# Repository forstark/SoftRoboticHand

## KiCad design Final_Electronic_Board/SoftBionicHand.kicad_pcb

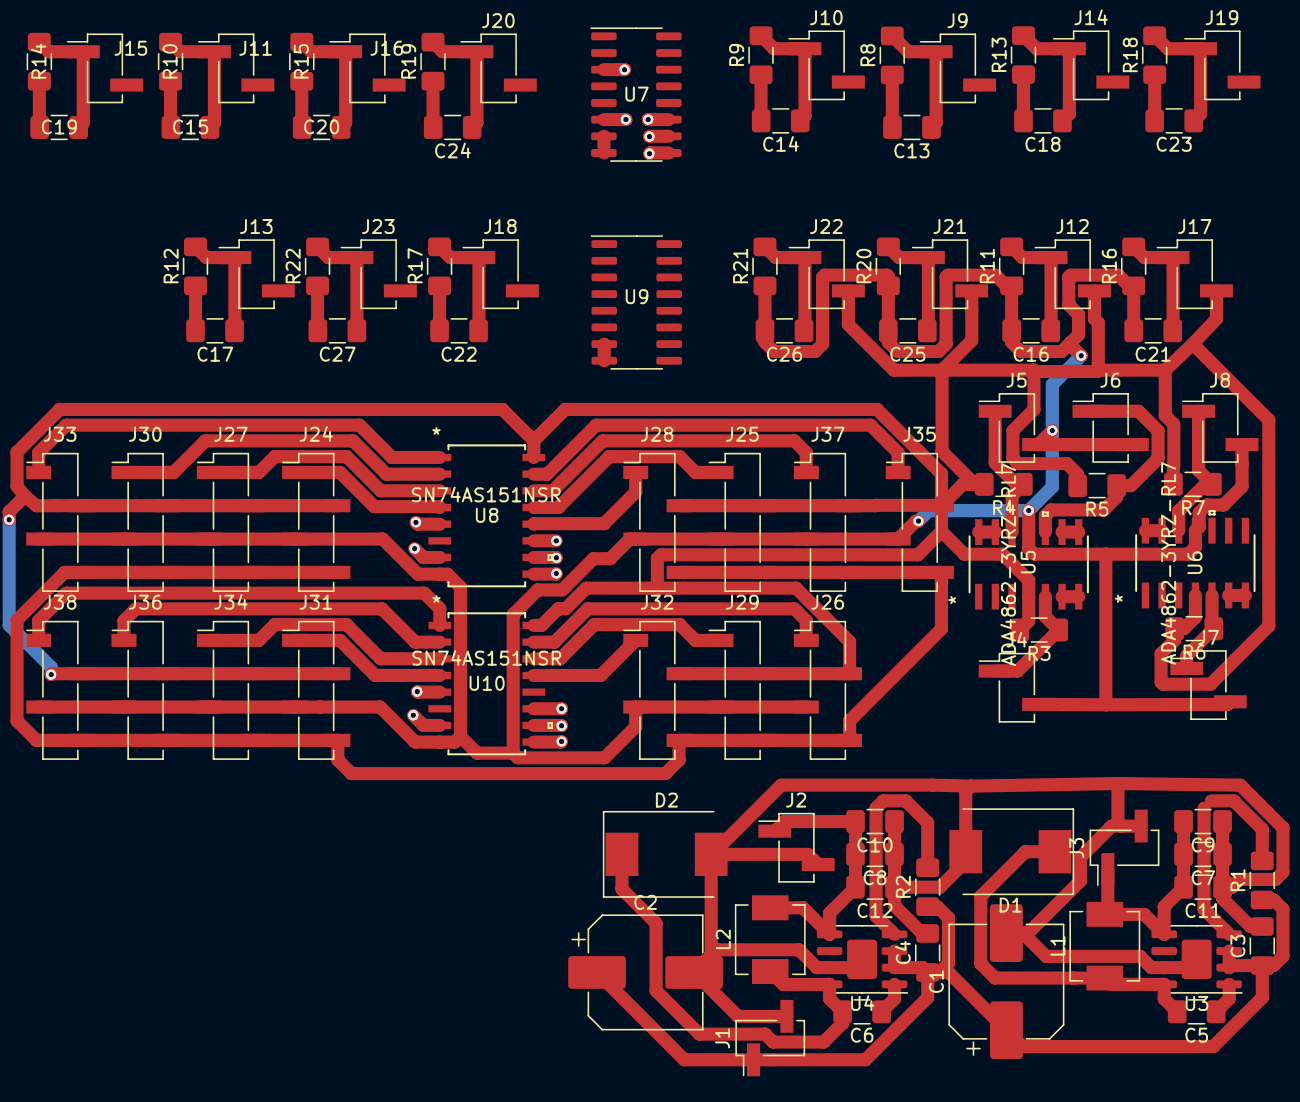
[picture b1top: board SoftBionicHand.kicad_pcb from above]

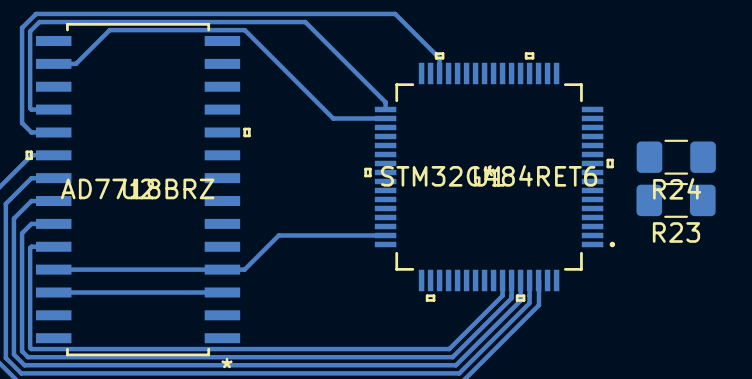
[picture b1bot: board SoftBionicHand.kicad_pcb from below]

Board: 2 copper layers, 103 parts (4 on the bottom side), 84 nets.

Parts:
C1, C2: 100uF/50V; CP_Elec_8x10.5
C3, C4: 10uF/50V; C_1206_3216Metric_Pad1.42x1.75mm_HandSolder
C5, C6, C13, C14, C15, C16, C17, C18, C19, C20, C21, C22, C23, C24, C25, C26, C27: 0.1uF/50V; C_1206_3216Metric_Pad1.42x1.75mm_HandSolder
C7, C8, C9, C10: 22uF/25V; C_1206_3216Metric_Pad1.42x1.75mm_HandSolder
C11, C12: 1uF/50V; C_1206_3216Metric_Pad1.42x1.75mm_HandSolder
D1, D2: B330; D_SMC
J1: Conn_Vin; PinHeader_1x02_P2.54mm_Vertical_SMD_Pin1Left
J2: Conn_Vout_3.3V; PinHeader_1x02_P2.54mm_Vertical_SMD_Pin1Left
J3: Conn_Vout_5V; PinHeader_1x02_P2.54mm_Vertical_SMD_Pin1Left
J4: Conn_FLEX_1; PinHeader_1x02_P2.54mm_Vertical_SMD_Pin1Left
J5: Conn_FLEX_2; PinHeader_1x02_P2.54mm_Vertical_SMD_Pin1Left
J6: Conn_FLEX_3; PinHeader_1x02_P2.54mm_Vertical_SMD_Pin1Left
J7: Conn_FLEX_4; PinHeader_1x02_P2.54mm_Vertical_SMD_Pin1Left
J8: Conn_FLEX_5; PinHeader_1x02_P2.54mm_Vertical_SMD_Pin1Left
J9: Conn_STR_1; PinHeader_1x02_P2.54mm_Vertical_SMD_Pin1Left
J10: Conn_STR_4; PinHeader_1x02_P2.54mm_Vertical_SMD_Pin1Left
J11: Conn_STR_7; PinHeader_1x02_P2.54mm_Vertical_SMD_Pin1Left
J12: Conn_STR_10; PinHeader_1x02_P2.54mm_Vertical_SMD_Pin1Left
J13: Conn_STR_13; PinHeader_1x02_P2.54mm_Vertical_SMD_Pin1Left
J14: Conn_STR_2; PinHeader_1x02_P2.54mm_Vertical_SMD_Pin1Left
J15: Conn_STR_5; PinHeader_1x02_P2.54mm_Vertical_SMD_Pin1Left
J16: Conn_STR_8; PinHeader_1x02_P2.54mm_Vertical_SMD_Pin1Left
J17: Conn_STR_11; PinHeader_1x02_P2.54mm_Vertical_SMD_Pin1Left
J18: Conn_STR_14; PinHeader_1x02_P2.54mm_Vertical_SMD_Pin1Left
J19: Conn_STR_3; PinHeader_1x02_P2.54mm_Vertical_SMD_Pin1Left
J20: Conn_STR_6; PinHeader_1x02_P2.54mm_Vertical_SMD_Pin1Left
J21: Conn_STR_9; PinHeader_1x02_P2.54mm_Vertical_SMD_Pin1Left
J22: Conn_STR_12; PinHeader_1x02_P2.54mm_Vertical_SMD_Pin1Left
J23: Conn_STR_15; PinHeader_1x02_P2.54mm_Vertical_SMD_Pin1Left
J24: Conn_TEMP_1; PinSocket_1x04_P2.54mm_Vertical_SMD_Pin1Left
J25: Conn_TEMP_7; PinSocket_1x04_P2.54mm_Vertical_SMD_Pin1Left
J26: Conn_TEMP_13; PinSocket_1x04_P2.54mm_Vertical_SMD_Pin1Left
J27: Conn_TEMP_2; PinSocket_1x04_P2.54mm_Vertical_SMD_Pin1Left
J28: Conn_TEMP_8; PinSocket_1x04_P2.54mm_Vertical_SMD_Pin1Left
J29: Conn_TEMP_14; PinSocket_1x04_P2.54mm_Vertical_SMD_Pin1Left
J30: Conn_TEMP_3; PinSocket_1x04_P2.54mm_Vertical_SMD_Pin1Left
J31: Conn_TEMP_9; PinSocket_1x04_P2.54mm_Vertical_SMD_Pin1Left
J32: Conn_TEMP_15; PinSocket_1x04_P2.54mm_Vertical_SMD_Pin1Left
J33: Conn_TEMP_4; PinSocket_1x04_P2.54mm_Vertical_SMD_Pin1Left
J34: Conn_TEMP_10; PinSocket_1x04_P2.54mm_Vertical_SMD_Pin1Left
J35: Conn_TEMP_5; PinSocket_1x04_P2.54mm_Vertical_SMD_Pin1Left
J36: Conn_TEMP_11; PinSocket_1x04_P2.54mm_Vertical_SMD_Pin1Left
J37: Conn_TEMP_6; PinSocket_1x04_P2.54mm_Vertical_SMD_Pin1Left
J38: Conn_TEMP_12; PinSocket_1x04_P2.54mm_Vertical_SMD_Pin1Left
L1: 6.8uH; L_Vishay_IHLP-2020
L2: 4.7uH; L_Vishay_IHLP-2020
R1, R2: 100k; R_1206_3216Metric_Pad1.42x1.75mm_HandSolder
R3, R4, R5, R6, R7: 33k; R_1206_3216Metric_Pad1.42x1.75mm_HandSolder
R8, R9, R10, R11, R12, R13, R14, R15, R16, R17, R18, R19, R20, R21, R22: 330k; R_1206_3216Metric_Pad1.42x1.75mm_HandSolder
R23, R24: 10k; R_1206_3216Metric_Pad1.42x1.75mm_HandSolder
U1: STM32G484RET6
U2: AD7718BRZ
U3, U4: ADP2303ARDZ-5.0; SOIC-8-1EP_3.9x4.9mm_P1.27mm_EP2.29x3mm
U5, U6: ADA4862-3YRZ-RL7
U7, U9: CD4051B; SOIC-16_3.9x9.9mm_P1.27mm
U8, U10: SN74AS151NSR

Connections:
3.3V: C8.2, C10.2, C12.2, J2.1, L2.2, U1.16, U1.29, U1.32, U1.48, U1.64, U4.5
5V: C7.2, C9.2, C11.2, J3.1, L1.2, U3.5
+5V: J9.2, J10.2, J11.2, J12.2, J13.2, J14.2, J15.2, J16.2, J17.2, J18.2, J19.2, J20.2, J21.2, J22.2, J23.2, J24.2, J25.2, J26.2, J27.2, J28.2, J29.2, J30.2, J31.2, J32.2, J33.2, J34.2, J35.2, J36.2, J37.2, J38.2, R3.2, R4.2, R5.2, R6.2, R7.2, R23.1, R24.1, U2.3, U2.26, U5.4, U6.4, U7.16, U8.16, U9.16, U10.16
+12V: C1.1, C2.1, C3.1, C4.1, J1.1, R1.1, R2.1, U3.2, U3.3, U4.2, U4.3
/Mux_sensors/FLEX_SENSOR_1: J4.1, R3.1, U5.5
/Mux_sensors/FLEX_SENSOR_2: J5.1, R4.1, U5.12
/Mux_sensors/FLEX_SENSOR_3: J6.1, R5.1, U5.10
/Mux_sensors/FLEX_SENSOR_4: J7.1, R6.1, U6.5
/Mux_sensors/FLEX_SENSOR_5: J8.1, R7.1, U6.12
ADC_CS: U1.61, U2.21
ADC_DIN: U1.58, U2.24
ADC_DOUT: U1.59, U2.23
ADC_P1: U1.33, U2.18
ADC_P2: U1.34, U2.16
ADC_RDY: U1.60, U2.22
ADC_RESET: U1.30, U2.19
ADC_SCLK: U1.62, U2.20
FLEX_SENSOR_AOP_1: U2.9, U5.6, U5.7
FLEX_SENSOR_AOP_2: U2.10, U5.13, U5.14
FLEX_SENSOR_AOP_3: U2.11, U5.8, U5.9
FLEX_SENSOR_AOP_4: U2.15, U6.6, U6.7
FLEX_SENSOR_AOP_5: U2.1, U6.13, U6.14
GND: C1.2, C2.2, C3.2, C4.2, C7.1, C8.1, C9.1, C10.1, C11.1, C12.1, C13.2, C14.2, C15.2, C16.2, C17.2, C18.2, C19.2, C20.2, C21.2, C22.2, C23.2, C24.2, C25.2, C26.2, C27.2, D1.2, D2.2, J1.2, J2.2, J3.2, J4.2, J5.2, J6.2, J7.2, J8.2, J24.3, J25.3, J26.3, J27.3, J28.3, J29.3, J30.3, J31.3, J32.3, J33.3, J34.3, J35.3, J36.3, J37.3, J38.3, R8.1, R9.1, R10.1, R11.1, R12.1, R13.1, R14.1, R15.1, R16.1, R17.1, R18.1, R19.1, R20.1, R21.1, R22.1, U1.15, U1.27, U1.31, U1.47, U1.63, U2.4, U2.17, U2.25, U3.7, U3.9, U4.7, U4.9, U5.11, U6.11, U7.7, U7.8, U8.8, U9.7, U9.8, U10.8
MUX_1_EN: U1.46, U7.6
MUX_2_EN: U1.49, U9.6
MUX_3_EN: U1.50, U8.7
MUX_4_EN: U1.51, U10.7
MUX_IN_1_A: U1.12, U7.11
MUX_IN_1_B: U1.13, U7.10
MUX_IN_1_C: U1.14, U7.9
MUX_IN_2_A: U1.17, U9.11
MUX_IN_2_B: U1.18, U9.10
MUX_IN_2_C: U1.19, U9.9
MUX_IN_3_A: U1.20, U8.11
MUX_IN_3_B: U1.21, U8.10
MUX_IN_3_C: U1.42, U8.9
MUX_IN_4_A: U1.43, U10.11
MUX_IN_4_B: U1.44, U10.10
MUX_IN_4_C: U1.45, U10.9
MUX_SDA_TEMP_1_0: J24.1, U8.4
MUX_SDA_TEMP_1_1: J27.1, U8.3
MUX_SDA_TEMP_1_2: J30.1, U8.2
MUX_SDA_TEMP_2_0: J33.1, U8.1
MUX_SDA_TEMP_2_1: J35.1, U8.15
MUX_SDA_TEMP_2_2: J37.1, U8.14
MUX_SDA_TEMP_3_0: J25.1, U8.13
MUX_SDA_TEMP_3_1: J28.1, U8.12
MUX_SDA_TEMP_3_2: J31.1, U10.4
MUX_SDA_TEMP_4_0: J34.1, U10.3
MUX_SDA_TEMP_4_1: J36.1, U10.2
MUX_SDA_TEMP_4_2: J38.1, U10.1
MUX_SDA_TEMP_5_0: J26.1, U10.15
MUX_SDA_TEMP_5_1: J29.1, U10.14
MUX_SDA_TEMP_5_2: J32.1, U10.13
MUX_SENSOR_STR_1_0: C13.1, J9.1, R8.2, U7.13
MUX_SENSOR_STR_1_1: C18.1, J14.1, R13.2, U7.14
MUX_SENSOR_STR_1_2: C23.1, J19.1, R18.2, U7.15
MUX_SENSOR_STR_2_0: C14.1, J10.1, R9.2, U7.12
MUX_SENSOR_STR_2_1: C19.1, J15.1, R14.2, U7.1
MUX_SENSOR_STR_2_2: C24.1, J20.1, R19.2, U7.5
MUX_SENSOR_STR_3_0: C15.1, J11.1, R10.2, U7.2
MUX_SENSOR_STR_3_1: C20.1, J16.1, R15.2, U7.4
MUX_SENSOR_STR_3_2: C25.1, J21.1, R20.2, U9.13
MUX_SENSOR_STR_4_0: C16.1, J12.1, R11.2, U9.14
MUX_SENSOR_STR_4_1: C21.1, J17.1, R16.2, U9.15
MUX_SENSOR_STR_4_2: C26.1, J22.1, R21.2, U9.12
MUX_SENSOR_STR_5_0: C17.1, J13.1, R12.2, U9.1
MUX_SENSOR_STR_5_1: C22.1, J18.1, R17.2, U9.5
MUX_SENSOR_STR_5_2: C27.1, J23.1, R22.2, U9.2
unnamed: C5.1, U3.1
unnamed: C5.2, D1.1, L1.1, U3.8
unnamed: C6.1, U4.1
unnamed: C6.2, D2.1, L2.1, U4.8
unnamed: R1.2, U3.4
unnamed: R2.2, U4.4
OUT_MUX_1: U2.7, U7.3
OUT_MUX_2: U2.8, U9.3
OUT_MUX_3: R23.2, U1.8, U8.5, U10.5
PWR_DWN_AOP_A_1: U1.24, U5.1
PWR_DWN_AOP_A_2: U1.25, U5.2
PWR_DWN_AOP_A_3: U1.26, U5.3
PWR_DWN_AOP_B_1: U1.56, U6.1
PWR_DWN_AOP_B_2: U1.57, U6.2
SCL: J24.4, J25.4, J26.4, J27.4, J28.4, J29.4, J30.4, J31.4, J32.4, J33.4, J34.4, J35.4, J36.4, J37.4, J38.4, R24.2, U1.9

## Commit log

2021-03-29 TMP36
2021-03-29 Adding final electronic board
2021-03-29 TMP36 bis
2021-03-29 Updating temperature sensor code
2021-03-29 Adding flex sensors
2021-03-29 Updating flex sensors
2021-03-29 Name correction
2021-03-29 Adding temperature sensor
2021-03-30 Code flexion corrigé
2021-04-01 Auto stash before merge of "master" and "origin/main"
2021-04-01 Model_rasberry
2021-04-04 Ordering files
2021-04-04 Adding ordered files
2021-04-08 RaspberryV2
2021-04-09 Ajout des pièces solidworks pour les hats de la raspberry
2021-04-14 Detectiondescontours
2021-04-14 Delete Code_Capteurs directory
    old version
2021-04-14 Add files via upload
    new version
2021-04-15 Code Arduino pour les cinq doigt final
2021-04-15 Code Arduino final de chez final pour les doits
2021-04-15 Ajout code gestion des données des capteurs c++ STM32
2021-04-15 Gestion capteur temp pour code c++ STM32
2021-04-16 Détection contour image
2021-04-16 testcourfinal
2021-04-19 fusion2
2021-04-27 dernière version

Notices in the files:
parts and their libraries:
Copyright 2016 Accelerated Designs. All rights reserved.
